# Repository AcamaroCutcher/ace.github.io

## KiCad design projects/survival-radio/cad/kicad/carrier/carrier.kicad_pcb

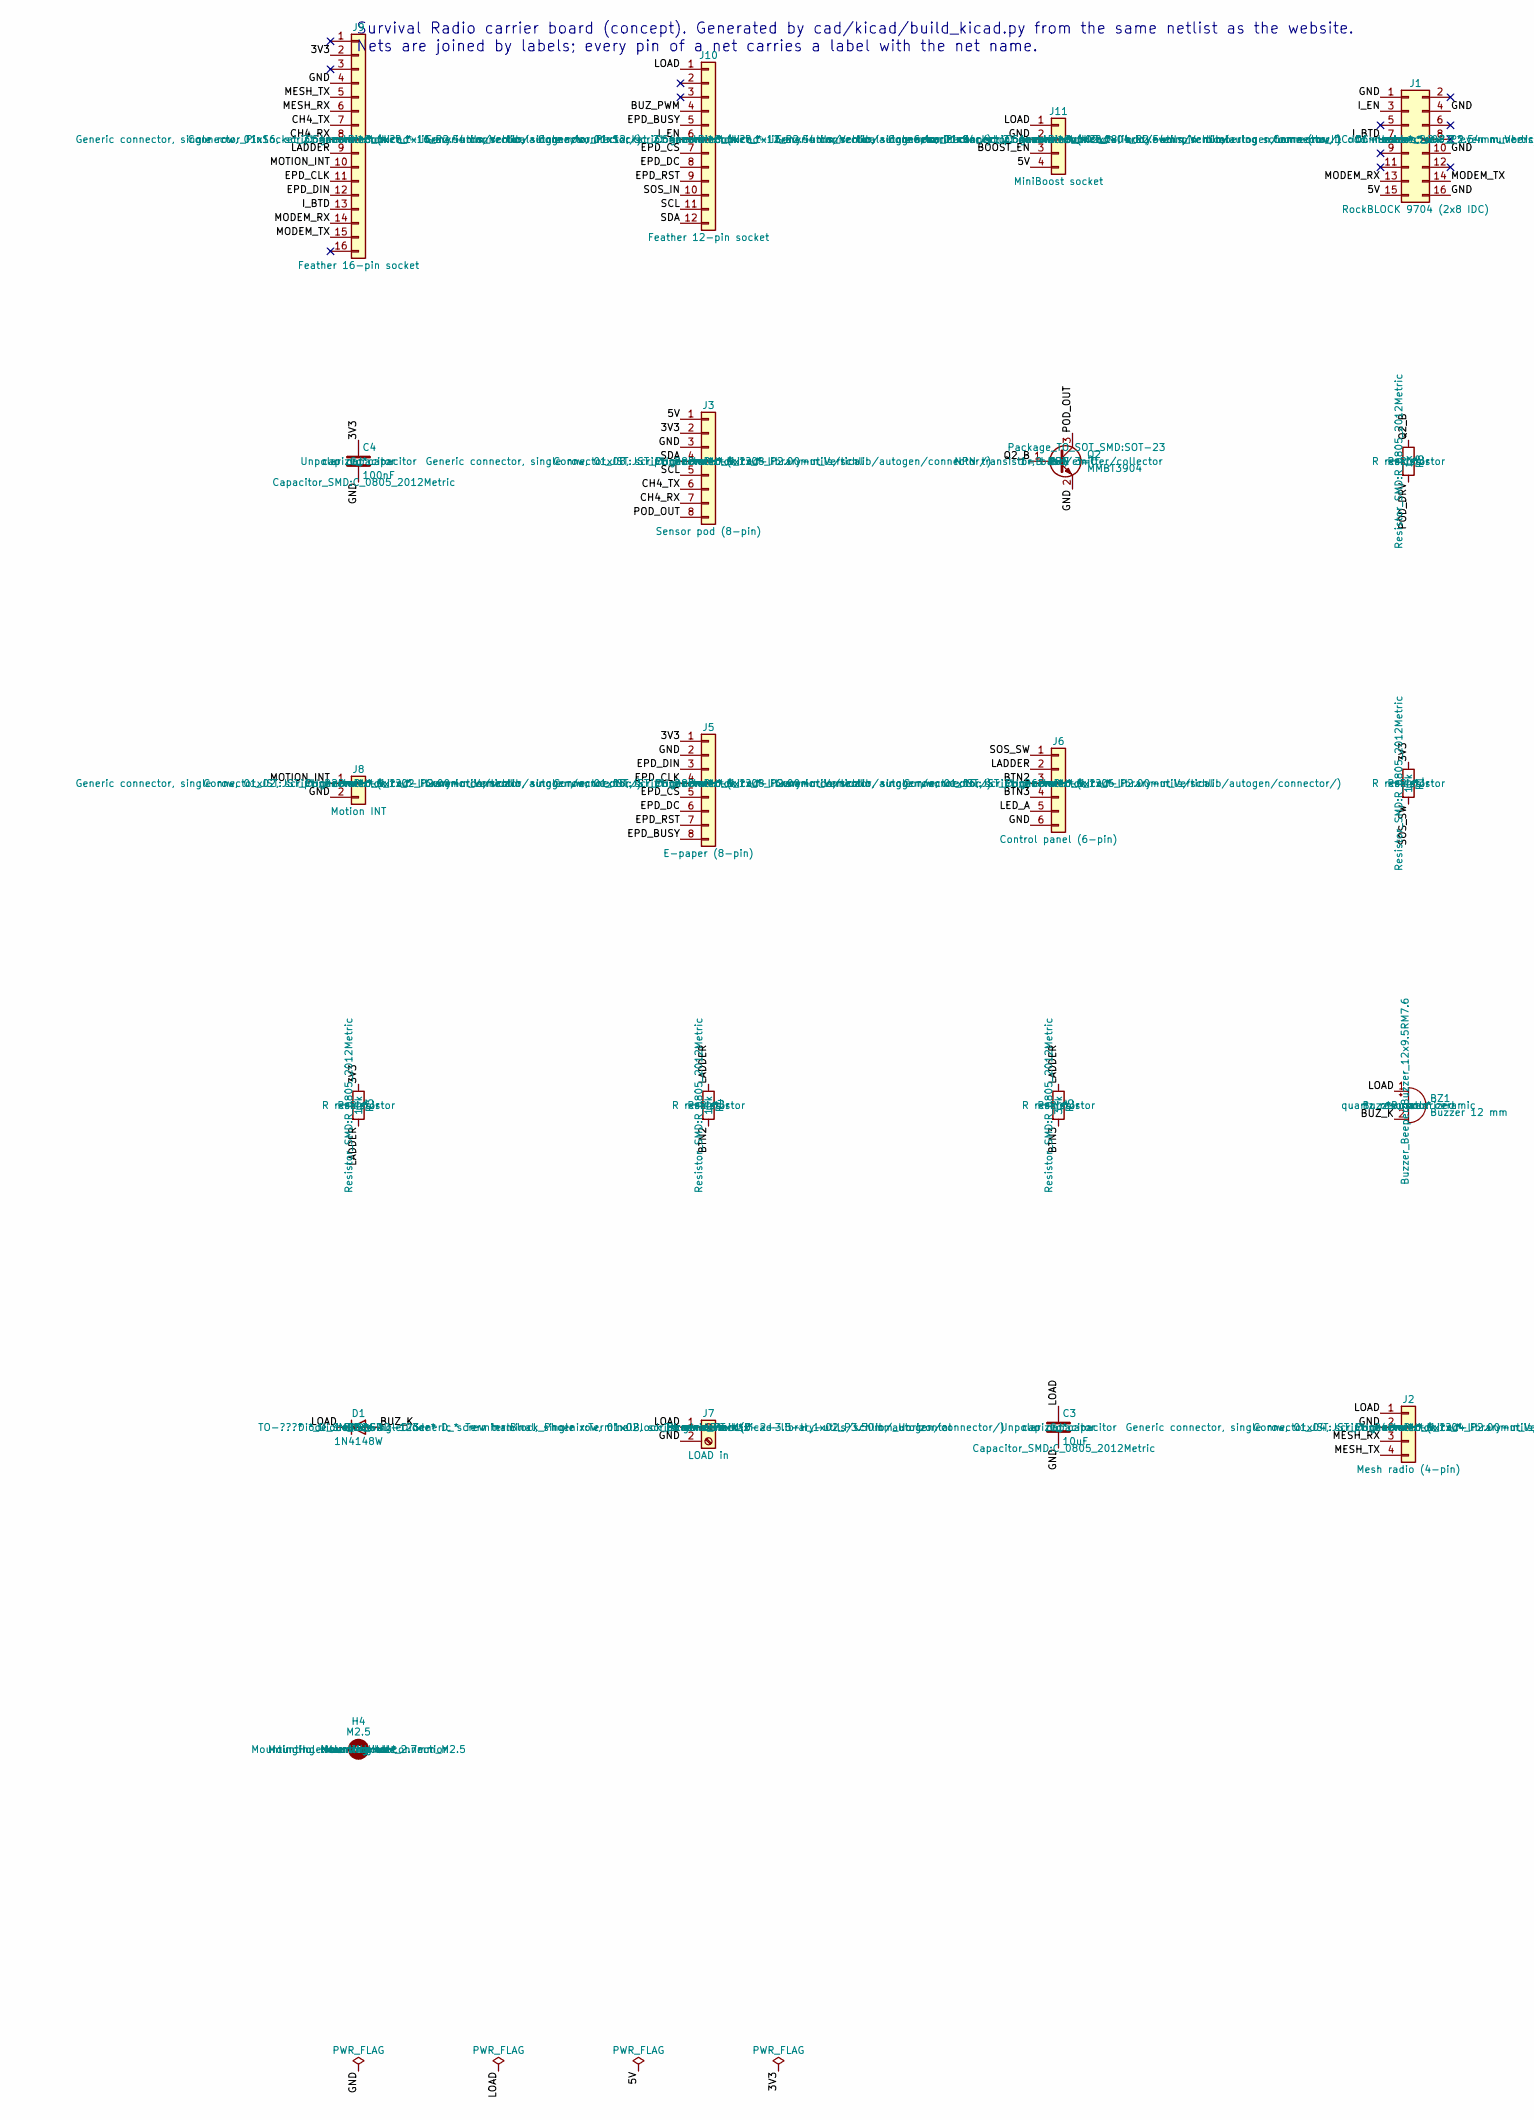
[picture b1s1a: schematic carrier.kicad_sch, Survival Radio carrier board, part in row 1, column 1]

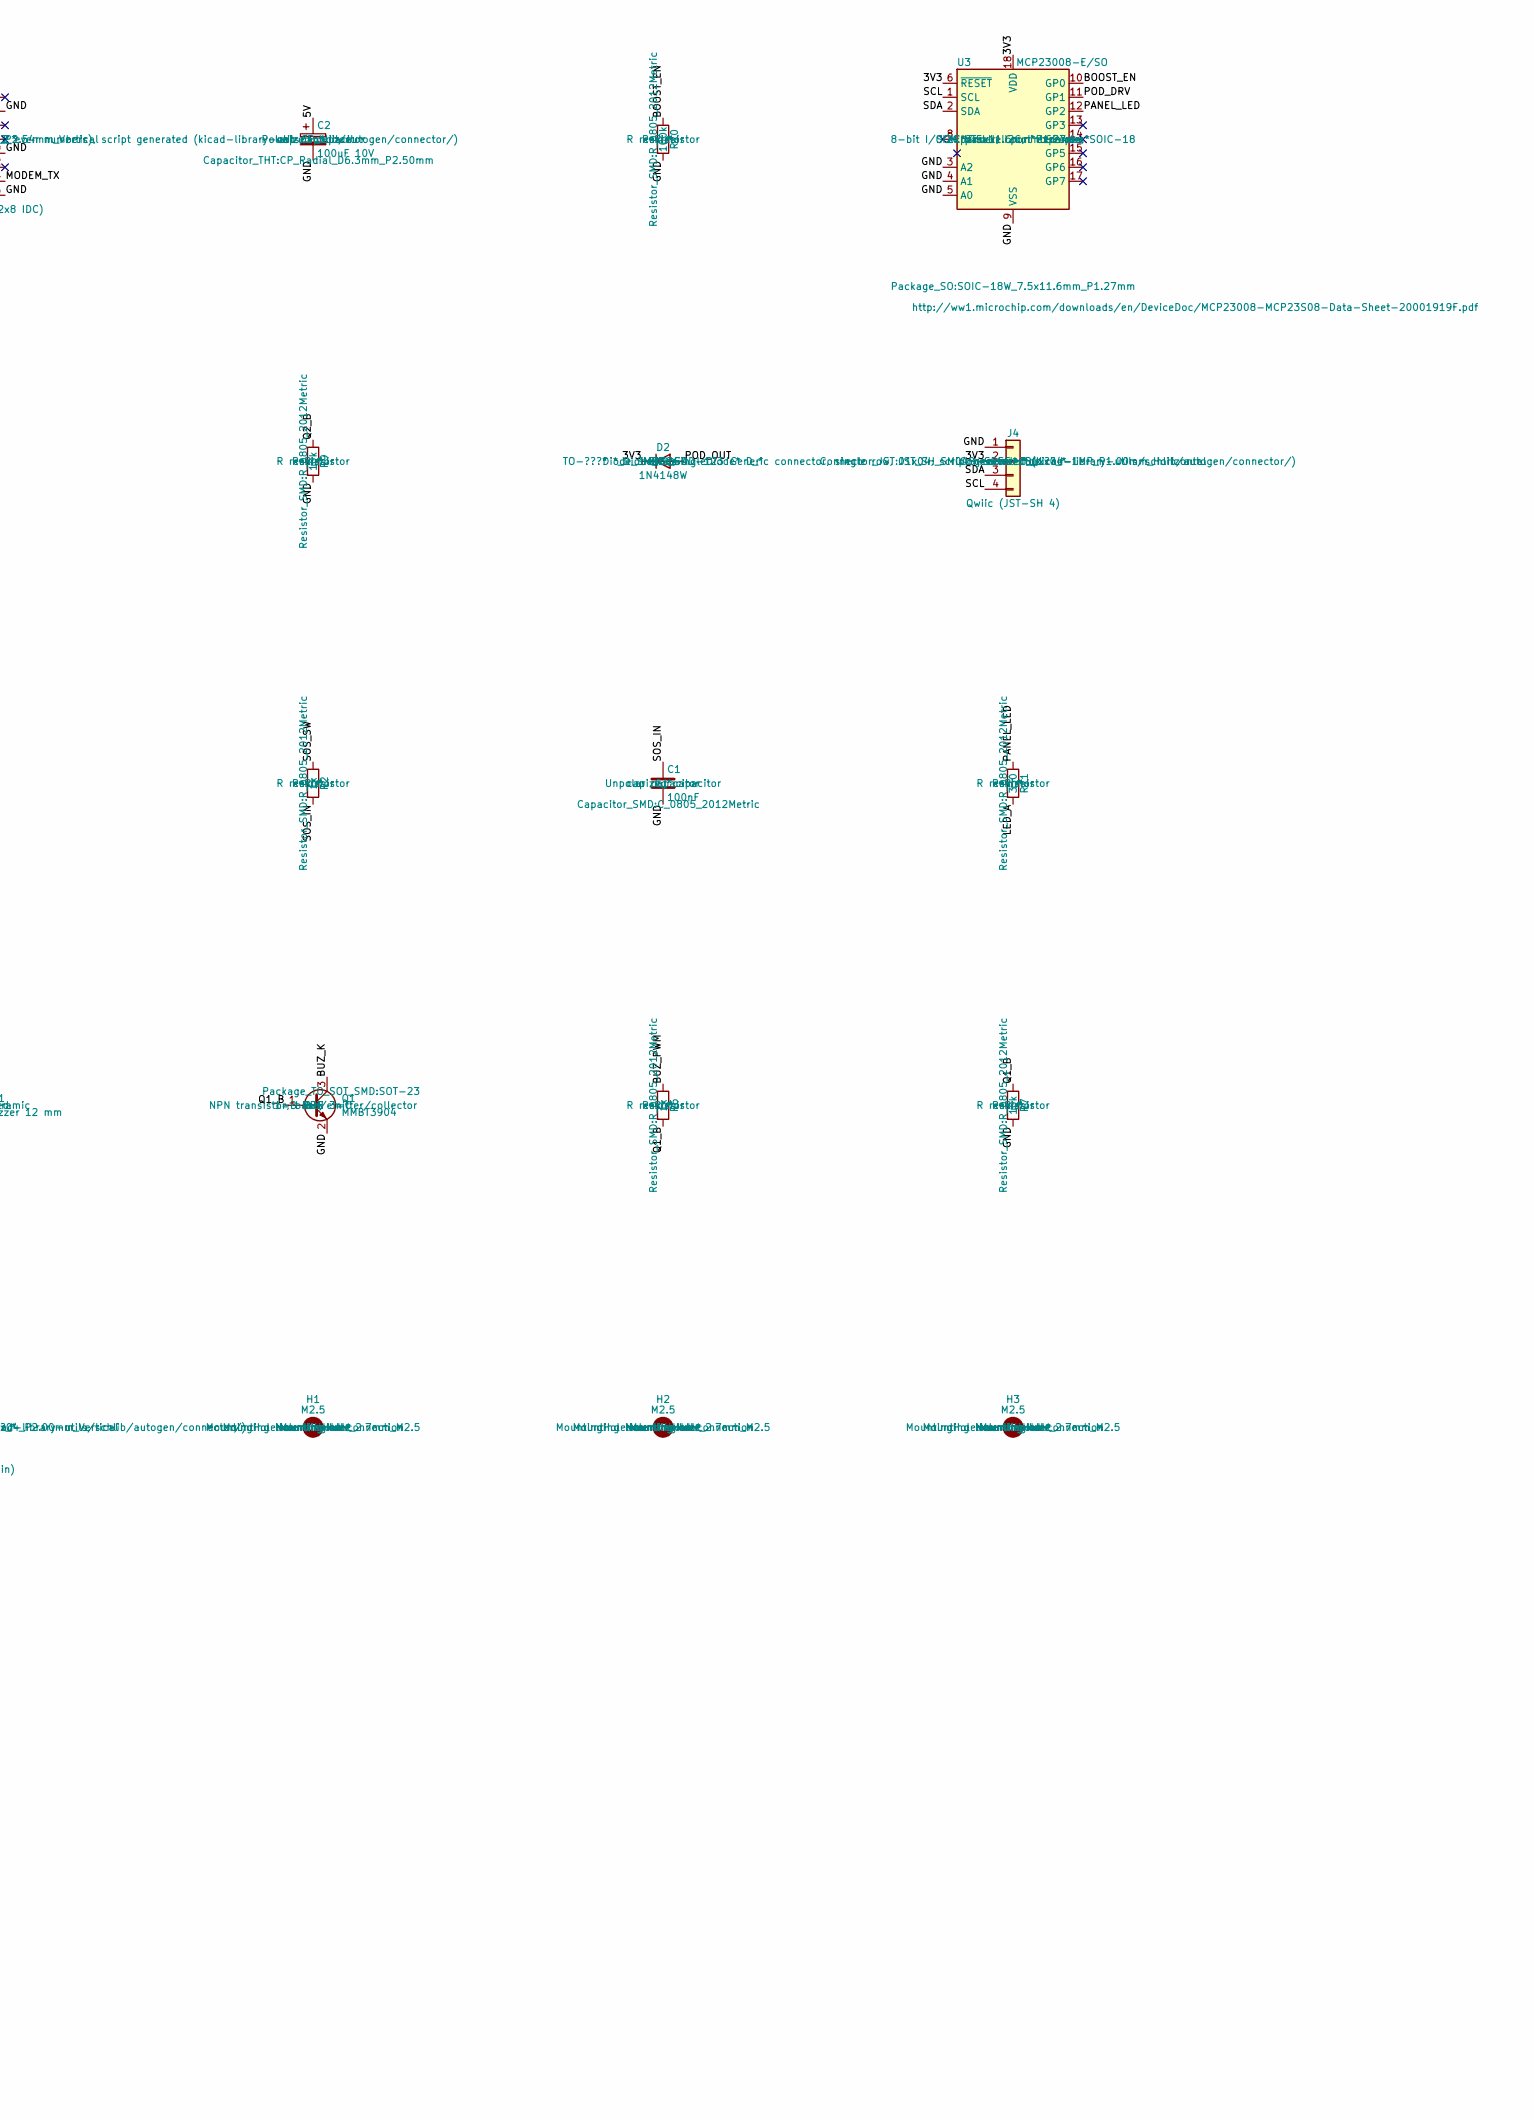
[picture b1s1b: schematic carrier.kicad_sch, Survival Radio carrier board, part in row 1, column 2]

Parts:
BZ1: Buzzer 12 mm; Buzzer_12x9.5RM7.6
C1, C4: 100nF; C_0805_2012Metric
C2: 100uF 10V; CP_Radial_D6.3mm_P2.50mm
C3: 10uF; C_0805_2012Metric
D1, D2: 1N4148W; D_SOD-123
H1, H2, H3, H4: M2.5; MountingHole_2.7mm_M2.5
J1: RockBLOCK 9704 (2x8 IDC); IDC-Header_2x08_P2.54mm_Vertical
J2: Mesh radio (4-pin); JST_PH_B4B-PH-K_1x04_P2.00mm_Vertical
J3: Sensor pod (8-pin); JST_PH_B8B-PH-K_1x08_P2.00mm_Vertical
J4: Qwiic (JST-SH 4); JST_SH_SM04B-SRSS-TB_1x04-1MP_P1.00mm_Horizontal
J5: E-paper (8-pin); JST_PH_B8B-PH-K_1x08_P2.00mm_Vertical
J6: Control panel (6-pin); JST_PH_B6B-PH-K_1x06_P2.00mm_Vertical
J7: LOAD in; TerminalBlock_Phoenix_PT-1,5-2-3.5-H_1x02_P3.50mm_Horizontal
J8: Motion INT; JST_PH_B2B-PH-K_1x02_P2.00mm_Vertical
J9: Feather 16-pin socket; PinSocket_1x16_P2.54mm_Vertical
J10: Feather 12-pin socket; PinSocket_1x12_P2.54mm_Vertical
J11: MiniBoost socket; PinSocket_1x04_P2.54mm_Vertical
Q1, Q2: MMBT3904; SOT-23
R1, R3, R4, R7, R9: 10k; R_0805_2012Metric
R2, R6, R8: 1k; R_0805_2012Metric
R5: 33k; R_0805_2012Metric
R10: 100k; R_0805_2012Metric
R11: 330; R_0805_2012Metric
U3: MCP23008-E/SO; SOIC-18W_7.5x11.6mm_P1.27mm

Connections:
/3V3: C4.1, D2.1 (K), J3.2, J4.2, J5.1, J9.2, R1.1, R3.1, U3.6 (~RESET), U3.18 (VDD)
/5V: C2.1, J1.15, J3.1, J11.4
/BOOST_EN: J11.3, R10.1, U3.10 (GP0)
/BTN2: J6.3, R4.2
/BTN3: J6.4, R5.2
/BUZ_K: BZ1.2 (-), D1.2 (A), Q1.3 (C)
/BUZ_PWM: J10.4, R6.1
/CH4_RX: J3.7, J9.8
/CH4_TX: J3.6, J9.7
/EPD_BUSY: J5.8, J10.5
/EPD_CLK: J5.4, J9.11
/EPD_CS: J5.5, J10.7
/EPD_DC: J5.6, J10.8
/EPD_DIN: J5.3, J9.12
/EPD_RST: J5.7, J10.9
/GND: C1.2, C2.2, C3.2, C4.2, J1.1, J1.4, J1.10, J1.16, J2.2, J3.3, J4.1, J5.2, J6.6, J7.2, J8.2, J9.4, J11.2, Q1.2 (E), Q2.2 (E), R7.2, R9.2, R10.2, U3.3 (A2), U3.4 (A1), U3.5 (A0), U3.9 (VSS)
/I_BTD: J1.7, J9.13
/I_EN: J1.3, J10.6
/LADDER: J6.2, J9.9, R3.2, R4.1, R5.1
/LED_A: J6.5, R11.2
/LOAD: BZ1.1 (+), C3.1, D1.1 (K), J2.1, J7.1, J10.1, J11.1
/MESH_RX: J2.3, J9.6
/MESH_TX: J2.4, J9.5
/MODEM_RX: J1.13, J9.14
/MODEM_TX: J1.14, J9.15
/MOTION_INT: J8.1, J9.10
/PANEL_LED: R11.1, U3.12 (GP2)
/POD_DRV: R8.2, U3.11 (GP1)
/POD_OUT: D2.2 (A), J3.8, Q2.3 (C)
/Q1_B: Q1.1 (B), R6.2, R7.1
/Q2_B: Q2.1 (B), R8.1, R9.1
/SCL: J3.5, J4.4, J10.11, U3.1 (SCL)
/SDA: J3.4, J4.3, J10.12, U3.2 (SDA)
/SOS_IN: C1.1, J10.10, R2.2
/SOS_SW: J6.1, R1.2, R2.1

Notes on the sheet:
Survival Radio carrier board (concept). Generated by cad/kicad/build_kicad.py from the same netlist as the website. Nets are joined by labels; every pin of a net carries a label with the net name.

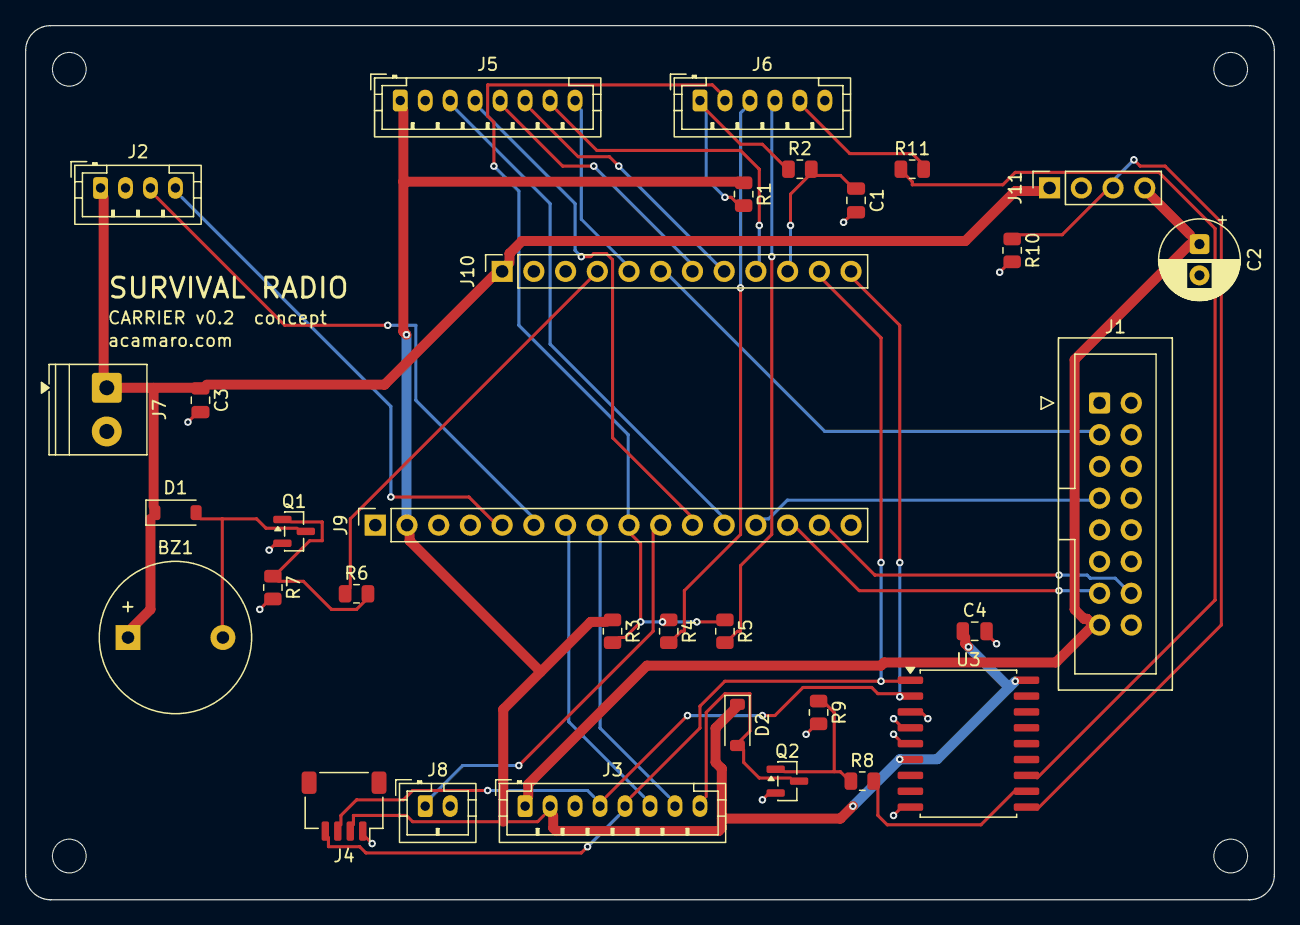
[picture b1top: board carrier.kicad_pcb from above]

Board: 2 copper layers, 100.0 x 70.0 mm, 36 parts (0 on the bottom side), 35 nets.

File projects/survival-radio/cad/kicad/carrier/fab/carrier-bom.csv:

"Reference","Value","Footprint","QUANTITY"
"BZ1","Buzzer 12 mm","Buzzer_Beeper:Buzzer_12x9.5RM7.6","1"
"C1,C4","100nF","Capacitor_SMD:C_0805_2012Metric","2"
"C2","100uF 10V","Capacitor_THT:CP_Radial_D6.3mm_P2.50mm","1"
"C3","10uF","Capacitor_SMD:C_0805_2012Metric","1"
"D1,D2","1N4148W","Diode_SMD:D_SOD-123","2"
"J1","RockBLOCK 9704 (2x8 IDC)","Connector_IDC:IDC-Header_2x08_P2.54mm_Vertical","1"
"J2","Mesh radio (4-pin)","Connector_JST:JST_PH_B4B-PH-K_1x04_P2.00mm_Vertical","1"
"J3","Sensor pod (8-pin)","Connector_JST:JST_PH_B8B-PH-K_1x08_P2.00mm_Vertical","1"
"J4","Qwiic (JST-SH 4)","Connector_JST:JST_SH_SM04B-SRSS-TB_1x04-1MP_P1.00mm_Horizontal","1"
"J5","E-paper (8-pin)","Connector_JST:JST_PH_B8B-PH-K_1x08_P2.00mm_Vertical","1"
"J6","Control panel (6-pin)","Connector_JST:JST_PH_B6B-PH-K_1x06_P2.00mm_Vertical","1"
"J7","LOAD in","TerminalBlock_Phoenix:TerminalBlock_Phoenix_PT-1,5-2-3.5-H_1x02_P3.50mm_Horizontal","1"
"J8","Motion INT","Connector_JST:JST_PH_B2B-PH-K_1x02_P2.00mm_Vertical","1"
"J9","Feather 16-pin socket","Connector_PinSocket_2.54mm:PinSocket_1x16_P2.54mm_Vertical","1"
"J10","Feather 12-pin socket","Connector_PinSocket_2.54mm:PinSocket_1x12_P2.54mm_Vertical","1"
"J11","MiniBoost socket","Connector_PinSocket_2.54mm:PinSocket_1x04_P2.54mm_Vertical","1"
"Q1,Q2","MMBT3904","Package_TO_SOT_SMD:SOT-23","2"
"R1,R3,R4,R7,R9","10k","Resistor_SMD:R_0805_2012Metric","5"
"R2,R6,R8","1k","Resistor_SMD:R_0805_2012Metric","3"
"R5","33k","Resistor_SMD:R_0805_2012Metric","1"
"R10","100k","Resistor_SMD:R_0805_2012Metric","1"
"R11","330","Resistor_SMD:R_0805_2012Metric","1"
"U3","MCP23008-E/SO","Package_SO:SOIC-18W_7.5x11.6mm_P1.27mm","1"

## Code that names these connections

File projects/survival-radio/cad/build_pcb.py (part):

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  '5V': ('power', 'Switched 5 V from the boost: RockBLOCK V_IN+ and the pod\'s particle and methane sensors.'),
  '3V3': ('power', 'The Feather\'s 3.3 V regulator output: logic, expander, Qwiic chain, e-paper, pod I²C sensors.'),
  'SDA': ('i2c', 'I²C data: Feather ↔ expander ↔ Qwiic chain ↔ sensor pod.'), 'SCL': ('i2c', 'I²C clock, driven by the Feather.'),
  'BOOST_EN': ('gpio', 'Expander GP0 → boost EN. HIGH turns the 5 V rail on.'),
  'MODEM_TX': ('uart', 'UART 1: Feather TX → RockBLOCK RXD (pin 14), 230400 baud.'), 'MODEM_RX': ('uart', 'UART 1: RockBLOCK TXD (pin 13) → Feather RX.'),
  'I_EN': ('gpio', 'Modem enable: D11 → RockBLOCK pin 3.'), 'I_BTD': ('gpio', 'Modem "booted": RockBLOCK pin 7 → MI (GPIO37).'),
  'MESH_TX': ('uart', 'UART 2: Feather A0 → mesh radio RXD1.'), 'MESH_RX': ('uart', 'UART 2: mesh radio TXD1 → Feather A1.'),
  'CH4_TX': ('uart', 'UART 3: Feather A2 → methane sensor RX (via pod cable).'), 'CH4_RX': ('uart', 'UART 3: methane sensor TX → Feather A3.'),
  'EPD_CLK': ('spi', 'SPI clock to the e-paper.'), 'EPD_DIN': ('spi', 'SPI data to the e-paper.'), 'EPD_CS': ('spi', 'E-paper chip select (active LOW).'),
  'EPD_DC': ('spi', 'E-paper data / command select.'), 'EPD_RST': ('spi', 'E-paper reset.'), 'EPD_BUSY': ('spi', 'E-paper busy flag.'),
  'SOS_SW': ('gpio', 'SOS switch line, pulled up by R1; the switch pulls it to ground.'), 'SOS_IN': ('gpio', 'Filtered SOS line into D5 (wakes the ESP32-S3 from deep sleep).'),
  'LADDER': ('gpio', 'Button ladder node into A4 (analog).'), 'BTN2': ('gpio', 'Button 2 through R4.'), 'BTN3': ('gpio', 'Button 3 through R5.'),
  'PANEL_LED': ('gpio', 'Expander GP2 → R11.'), 'LED_A': ('gpio', 'Panel LED anode.'),
  'BUZ_PWM': ('gpio', 'D13 PWM → R6.'), 'Q1_B': ('gpio', 'Q1 base.'), 'BUZ_K': ('gpio', 'Buzzer low side, switched by Q1.'),
  'POD_DRV': ('gpio', 'Expander GP1 → R8.'), 'Q2_B': ('gpio', 'Q2 base.'), 'POD_OUT': ('gpio', 'Pod LED / vibration low side, switched by Q2.'),
  'MOTION_INT': ('gpio', 'LIS3DH INT1 → A5 (wake on motion).'),
}
POWER = {'LOAD', '5V', '3V3'}
padmap = {f"{p['ref']}.{p['pin']}": p for p in pads}
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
